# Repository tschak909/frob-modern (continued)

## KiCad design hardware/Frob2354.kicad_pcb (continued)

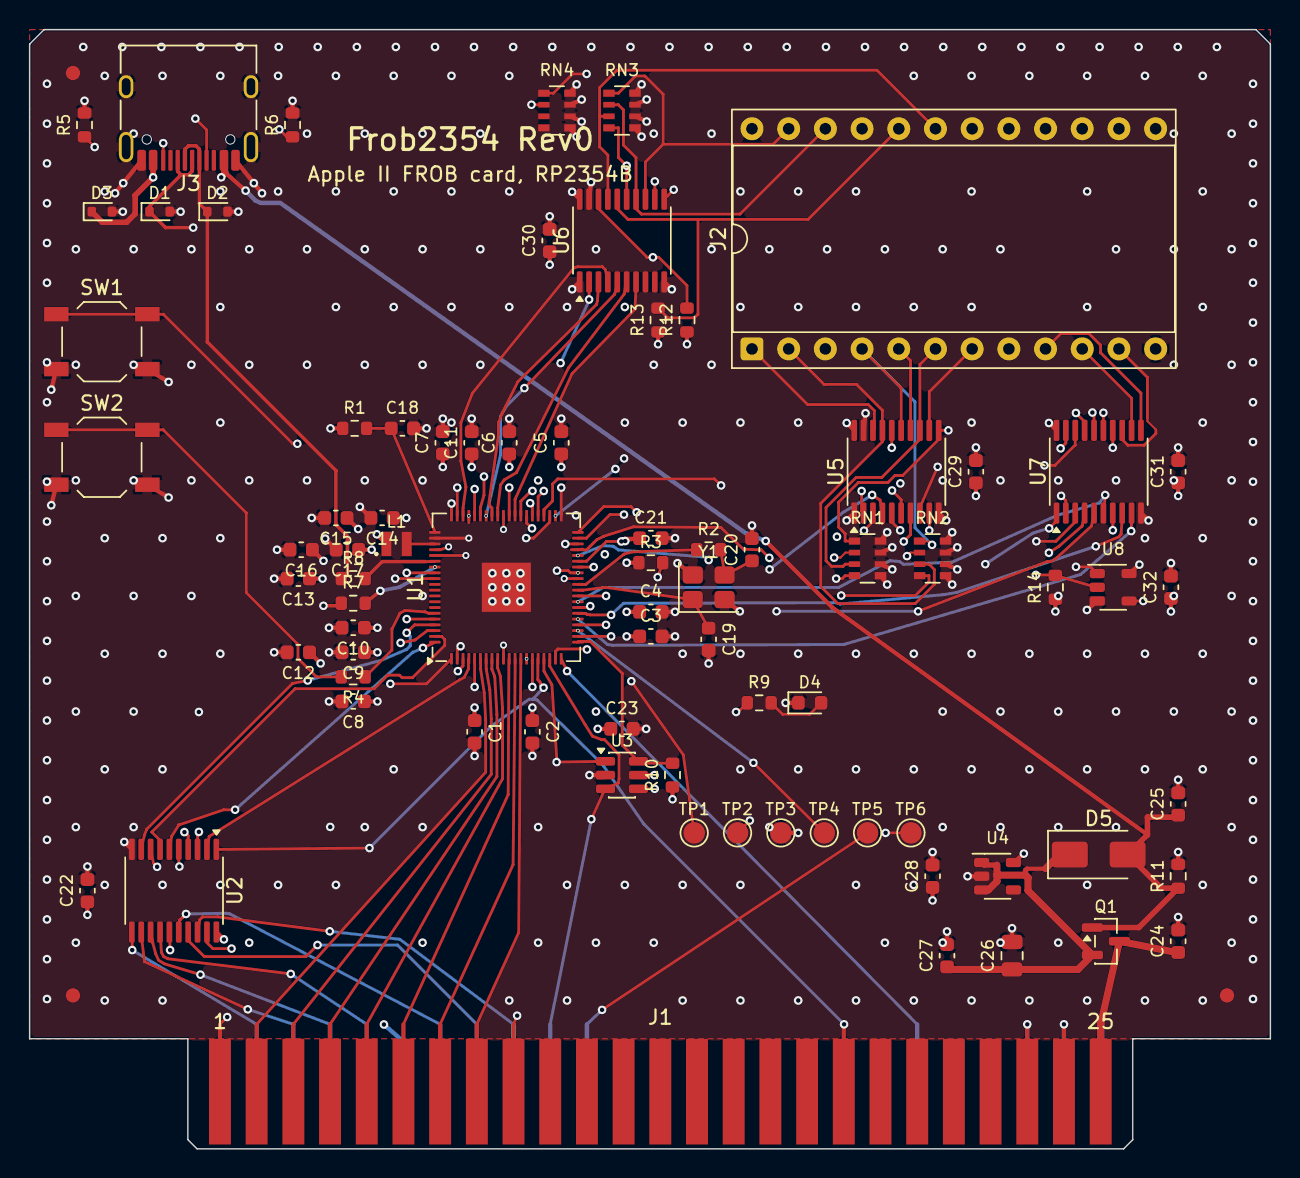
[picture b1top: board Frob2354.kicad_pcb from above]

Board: 6 copper layers, 85.9 x 77.5 mm, 80 parts (0 on the bottom side), 107 nets.

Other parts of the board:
FID1, FID2, FID3: Fiducial_1mm_Mask2mm

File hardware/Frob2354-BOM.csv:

"Refs","Value","Footprint","MPN","LCSC","Description","Assembly"
"C1,C2,C3,C4,C5,C6,C7,C8,C9,C10,C11,C14,C15,C16,C21,C22,C23,C24,C29,C30,C31,C32","100nF","C_0603_1608Metric","CC0603KRX7R9BB104","C14663","IOVDD decoupling","JLCPCB"
"C12,C28","10uF","C_0603_1608Metric","CL10A106KP8NNNC","C19702","3.3V bulk at the RP","JLCPCB"
"C13,C17,C18","4.7uF","C_0603_1608Metric","CL10A475KO8NNNC","C19666","VREG_VIN bulk","JLCPCB"
"C19,C20","15pF","C_0603_1608Metric","CL10C150JB8NNNC","C1644","crystal load","JLCPCB"
"C25,C27","1uF","C_0603_1608Metric","CL10A105KB8NNNC","C15849","VBUS decoupling","JLCPCB"
"C26","22uF","C_0805_2012Metric","CL21A226MAQNNNE","C45783","+5V bulk","JLCPCB"
"D1,D2,D3","ESD5Z5.0T1G","D_SOD-523","ESD5Z5.0T1G","C82044","USB ESD","JLCPCB"
"D4","green","LED_0603_1608Metric","KT-0603G","C12624","status LED (GP22)","JLCPCB"
"D5","SS34","D_SMA","SS34","C8678","USB VBUS OR-ing (no back-feed into the Apple)","JLCPCB"
"J2","FROB cable","DIP-24_W15.24mm_Socket","110-43-624-41-001000","","2600 cable socket, DIP-24 0.6 in (original FROB J2 pin-out); hand-solder","hand-solder"
"J3","USB-C","USB_C_Receptacle_HRO_TYPE-C-31-M-12","TYPE-C-31-M-12","C165948","firmware update / bench power","JLCPCB"
"L1","3.3uH","RPI_L_AOTA-B201610S3R3","AOTA-B201610S3R3-101-T","C42411119","RP2350 core SMPS inductor","JLCPCB"
"Q1","AO3401A","SOT-23","AO3401A","C15127","slot 5V switch: G = VBUS, S = +5V, D = SLOT_5V","JLCPCB"
"R1","33R","R_0603_1608Metric","0603WAF330JT5E","C23140","VREG_AVDD filter","JLCPCB"
"R2,R4,R9","1k","R_0603_1608Metric","0603WAF1001T5E","C21190","crystal drive limit","JLCPCB"
"R3,R10,R12,R13,R14","10k","R_0603_1608Metric","0603WAF1002T5E","C25804","RUN pull-up","JLCPCB"
"R5,R6","5.1k","R_0603_1608Metric","0603WAF5101T5E","C23186","UFP Rd","JLCPCB"
"R7,R8","27R","R_0603_1608Metric","0603WAF270JT5E","C25190","USB series","JLCPCB"
"R11","100k","R_0603_1608Metric","0603WAF1003T5E","C25803","holds the P-FET gate low without USB","JLCPCB"
"RN1,RN2,RN3,RN4","4x100k","R_Array_Convex_4x0603","4D03WGJ0104T5E","C1996","2600 address pull-downs: defined inputs with the cable unplugged","JLCPCB"
"SW1","RESET","SW_SPST_TL3342","TL3342F160QG","C2886898","RP2354B reset (RUN)","JLCPCB"
"SW2","BOOTSEL","SW_SPST_TL3342","TL3342F160QG","C2886898","RP2354B BOOTSEL: hold while pressing RESET (or plugging USB) for the UF2 drive","JLCPCB"
"U1","RP2354B","QFN-80-1EP_10x10mm_P0.4mm_EP3.4x3.4mm","RP2354B","C39843328","RP2350B + 2MB flash: FROB RAM, control/status and mailbox registers, both buses","JLCPCB"
"U2,U5,U6,U7","74LVC245A","TSSOP-20_4.4x6.5mm_P0.65mm","SN74LVC245APWR","C7848","Apple D0-D7 buffer: DIR = R/W, enabled only during this slot's /IOSEL or /DEVSEL","JLCPCB"
"U3","74LVC1G0832","SOT-23-6","SN74LVC1G0832DBVR","C206101","Apple buffer /OE = (/IOSEL & /DEVSEL) | A2_DOE_N","JLCPCB"
"U4","AP2112K-3.3","SOT-23-5","AP2112K-3.3TRG1","C51118","3.3V LDO, 600mA, fast start: every 3.3V load","JLCPCB"
"U8","74LVC1G32","SOT-23-5","SN74LVC1G32DBVR","C10096","2600 data buffer /OE = /CE | V_DOE_N","JLCPCB"
"Y1","12MHz","Crystal_SMD_3225-4Pin_3.2x2.5mm","ABM8-272-T3","C20625731","","JLCPCB"

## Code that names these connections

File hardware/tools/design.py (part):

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    supply (the console's), so everything the cable touches is an Ioff,
    5 V-tolerant LVC input on the card's 3.3 V, never an RP pad.

RP2350 datasheet, pin types: GPIO0-39 are "Digital IO (FT)" (5.5 V
tolerant provided IOVDD is at 3.3 V); GPIO40-47 are ADC-capable pads and NOT
5 V tolerant -- on this board they only ever see 3.3 V buffer outputs and a
3.3 V pull-up.  The slot signals wired to the RP directly are all on GP8-20.
"""
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# compares it with the generated netlist).
RP_GPIO_NET = {i: 'A2D_RP%d' % i for i in range(8)}             # A2_DATA_PIN 0: '245 A side
RP_GPIO_NET.update({8 + i: 'A2_A%d' % i for i in range(8)})     # A2_ADDR_PIN 8: slot A0-A7
RP_GPIO_NET.update({16: 'A2_RW', 17: 'A2_IOSEL_N', 18: 'A2_DEVSEL_N', 19: 'A2_PHI0',
                    20: 'A2_RES_N', 21: 'A2_DOE_N', 22: 'LED', 23: 'GP23'})
RP_GPIO_NET.update({24 + i: 'VD_RP%d' % i for i in range(8)})   # VCS_DATA_PIN 24: '245 A side
RP_GPIO_NET.update({32 + i: 'VA_RP%d' % i for i in range(12)})  # VCS_ADDR_PIN 32: buffered A0-A11
RP_GPIO_NET.update({44: 'VCE_RP_N', 45: 'V_DOE_N', 46: 'V_DIR', 47: 'VOE_RP_N'})
assert len(RP_GPIO_NET) == 48 and set(RP_GPIO_NET) == set(RP_GPIO_PIN)

# ---- Apple II peripheral slot (Apple II Reference Manual 1979, p.106) ------
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VCS_D_PIN = {0: 9, 1: 10, 2: 11, 3: 13, 4: 14, 5: 15, 6: 16, 7: 17}
J2_PINS = {VCS_A_PIN[i]: 'VCS_A%d' % i for i in VCS_A_PIN}
J2_PINS.update({VCS_D_PIN[i]: 'VCS_D%d' % i for i in VCS_D_PIN})
J2_PINS.update({18: 'VCS_CE_N', 20: 'VCS_OE_N', 12: 'GND', 24: NC})
assert sorted(J2_PINS) == list(range(1, 25))

# ---- common parts -----------------------------------------------------------
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      70: NC, 71: NC, 72: NC, 73: NC, 74: NC,                                # QSPI (flash in package)
      75: 'QSPI_SS', 81: 'GND'}
rp.update({p: RP_RAIL for p in RP_IOVDD_PINS})
rp.update({p: 'DVDD' for p in RP_DVDD_PINS})
for g, pin in RP_GPIO_PIN.items():
    rp[pin] = RP_GPIO_NET[g]
add('U', '%s:RP2354B_FROB' % LIB, 'RP2354B', FP('QFN-80-1EP_10x10mm_P0.4mm_EP3.4x3.4mm'), rp,
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
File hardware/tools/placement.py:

"""Component placement for gen_pcb.py: ref -> (x, y, rot).  Card body
x 117..202.88, y 25.4 (top edge) .. 95.25 (tab base); the fingers are on the
tab below, insertion edge y = 102.87.  Top view (component side), y down,
rotation CCW.  The rear of the Apple (back panel) is at +x.

Slot fingers (0.1 in, pin 1 at x 130.175):
  F.Cu  /IOSEL 130.2, A0-A7 132.7-150.5, R/W 173.4, INT/DMA OUT 186.1/188.6, +5V 191.1
  B.Cu  D0-D7 132.7-150.5, /DEVSEL 153.0, PHI0 155.6, /RES 178.4, INT/DMA IN 186.1/188.6, GND 191.1

Regions:
  centre        RP2354B at (150, 64) rot 90: Apple pins (GP4-20) face the fingers
                (south), GP0-3 + VREG/USB/QSPI west, 2600 address/controls
                (GP32-47) north, 2600 data + crystal + SWD/RUN east.  The core block
                (decoupling ring, VREG corner, crystal) is FujiNet-NES-Rev0's,
                which has the same package at the same rotation.
  south-west    Apple data '245 + select gate, by the D0-D7 fingers
  south-east    power entry by the +5V/GND fingers: P-FET, Schottky, LDO
  north-east    the FROB cable socket J2 (original card: top, toward the rear) and
                the three 2600 buffers between it and the RP
  north-west    USB-C on the top edge, ESD, CC; RESET/BOOTSEL buttons below it
"""


def do_placement(place):
    place('J1', 160.655, 102.87, 0)            # slot edge: tab centre, insertion edge

    # ---------------- RP2354B (FujiNet-NES-Rev0 core block) ----------------
    rx, ry = 150.0, 64.0
    place('U1', rx, ry, 90)
    RING = 10.0
    place('C1', rx - 2.2, ry + RING, 270)     # IOVDD 5   (pad 1 toward the chip)
    place('C2', rx + 1.8, ry + RING, 270)     # IOVDD 15
    place('C3', rx + RING, ry + 3.4, 0)       # IOVDD 24
    place('C4', rx + RING, ry + 1.7, 0)       # IOVDD 29
    place('R3', rx + RING, ry - 1.7, 0)       # RUN pull-up (pin 35)
    place('C21', rx + RING, ry - 3.4, 0)      # RUN power-on delay
    place('Y1', rx + RING + 4.0, ry - 0.0, 0)   # crystal: pad 1 XIN south-west, pad 3 XOUT_Y north-east
    place('C19', rx + RING + 4.0, ry + 3.6, 270)  # XIN load
    place('C20', rx + RING + 7.0, ry - 2.6, 90)   # XOUT_Y load
    place('R2', rx + RING + 4.0, ry - 2.6, 0)   # XOUT -> XOUT_Y
    place('C5', rx + 3.8, ry - RING, 90)      # IOVDD 41
    place('C6', rx + 0.2, ry - RING, 90)      # IOVDD 50
    place('C7', rx - 4.4, ry - RING, 90)      # IOVDD 60
    place('C11', rx - 2.4, ry - RING, 90)     # ADC_AVDD 59
    place('L1', rx - 7.6, ry - 3.0, 0)        # core inductor: pad 2 (LX) east toward pin 63
    place('C17', rx - 11.0, ry - 2.6, 180)    # core 4.7 uF
    place('C16', rx - 14.2, ry - 2.6, 180)    # DVDD 100 nF x3 in the DVDD lobe
    place('C14', rx - 8.6, ry - 4.8, 180)
    place('C15', rx - 11.8, ry - 4.8, 180)
    place('C13', rx - RING - 4.4, ry - 0.6, 180)  # VREG_VIN 4.7 uF
    place('R1', rx - 10.5, ry - 11.0, 0)      # 33R +3V3 -> VREG_AVDD
    place('C18', rx - 7.2, ry - 11.0, 0)      # VREG_AVDD 4.7 uF
    place('R8', rx - RING - 0.6, ry - 0.6, 0)     # USB_DM series (pin 66)
    place('R7', rx - RING - 0.6, ry + 1.1, 0)     # USB_DP series (pin 67)
    place('C10', rx - RING - 0.6, ry + 2.8, 180)  # USB_OTP_VDD (pin 68)
    place('C9', rx - RING - 0.6, ry + 4.5, 180)   # QSPI_IOVDD (pin 69)
    place('R4', rx - RING - 0.6, ry + 6.2, 180)   # QSPI_SS -> BOOTSEL button
    place('C8', rx - RING - 0.6, ry + 7.9, 180)   # IOVDD 76
    place('C12', rx - RING - 4.4, ry + 4.5, 180)  # 3.3V bulk 10 uF

    # ---------------- south-west: Apple data buffer + select gate ----------------
    place('U2', 127.0, 85.0, 270)             # '245: A side (RP) north, B side (slot D0-D7) south
    place('C22', 121.0, 85.0, 90)
    place('U3', 158.0, 77.0, 0)               # select gate: by /DEVSEL (153.0) and GP21; output west to U2
    place('C23', 158.0, 73.8, 0)
    place('R10', 161.5, 77.0, 90)             # A2_DOE_N pull-up

    # ---------------- south-east: power entry ----------------
    place('Q1', 191.5, 88.5, 0)               # P-FET at the +5V finger (x 191.1)
    place('C24', 196.5, 88.5, 90)             # SLOT_5V bypass
    place('R11', 196.5, 84.0, 90)             # P-FET gate pull-down
    place('D5', 191.0, 82.5, 0)               # SS34 VBUS -> +5V
    place('C26', 185.0, 89.5, 90)             # +5V bulk 22 uF
    place('U4', 184.0, 84.0, 0)               # LDO
    place('C27', 180.5, 89.5, 90)             # LDO in
    place('C28', 179.5, 84.0, 90)             # LDO out 10 uF
    place('C25', 196.5, 79.0, 90)             # VBUS 1 uF (at the P-FET end of the VBUS run)

    # ---------------- east: LED, test pads ----------------
    place('D4', 171.0, 72.0, 0)               # status LED (GP22)
    place('R9', 167.5, 72.0, 0)
    for i, tp in enumerate(('TP1', 'TP2', 'TP3', 'TP4', 'TP5', 'TP6')):
        place(tp, 163.0 + 3.0 * i, 81.0, 0)

    # ---------------- north-east: FROB cable socket + 2600 buffers ----------------
    place('J2', 167.0, 47.5, 90)              # pins 1-12 along +x at y 47.5, 13-24 at y 32.26
    place('U5', 177.0, 56.0, 90)              # A0-A7: A side (RP) south, B side (cable) north
    place('U7', 191.0, 56.0, 90)              # D0-D7
    place('U6', 158.0, 40.0, 90)              # A8-A11, /CE, /OE (top row of J2): A side south, B side north
    place('RN1', 175.0, 62.0, 0)              # A0-A3 pull-downs
    place('RN2', 179.5, 62.0, 0)              # A4-A7
    place('RN3', 158.0, 31.0, 0)              # A8-A11
    place('RN4', 153.5, 31.0, 0)              # spares
    place('C29', 182.5, 56.0, 90)             # U5 decoupling
    place('C30', 153.0, 40.0, 90)             # U6 decoupling
    place('C31', 196.5, 56.0, 90)             # U7 decoupling
    place('U8', 192.0, 64.0, 0)               # /OE = /CE | V_DOE_N
    place('C32', 196.0, 64.0, 90)
    place('R12', 162.5, 45.5, 90)             # /CE pull-up
    place('R13', 160.5, 45.5, 90)             # /OE pull-up
    place('R14', 188.0, 64.0, 90)             # V_DOE_N pull-up

    # ---------------- north-west: USB-C, buttons ----------------
    place('J3', 128.0, 30.4, 180)             # receptacle opening at the top edge
    place('R5', 120.8, 32.0, 90)              # CC1 Rd
    place('R6', 135.2, 32.0, 90)              # CC2 Rd
    place('D1', 126.0, 38.0, 0)               # ESD D+
    place('D2', 130.0, 38.0, 0)               # ESD D-
    place('D3', 122.0, 38.0, 0)               # ESD VBUS
    place('SW1', 122.0, 47.0, 0)              # RESET
    place('SW2', 122.0, 55.0, 0)              # BOOTSEL
